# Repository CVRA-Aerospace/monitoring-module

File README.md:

Rocket monitoring module
========================
This is a compact monitoring system.
It is used for monitoring a rocket.

Main features:
-------------
 - 3-axis gyroscope
 - Two 3-axis accelerometers (one for low g and one for high g accelerations)
 - 3-axis magnetometer
 - Barometer
 - ARM controller
 - microSD card
 - 1x CAN
 - 1x UART

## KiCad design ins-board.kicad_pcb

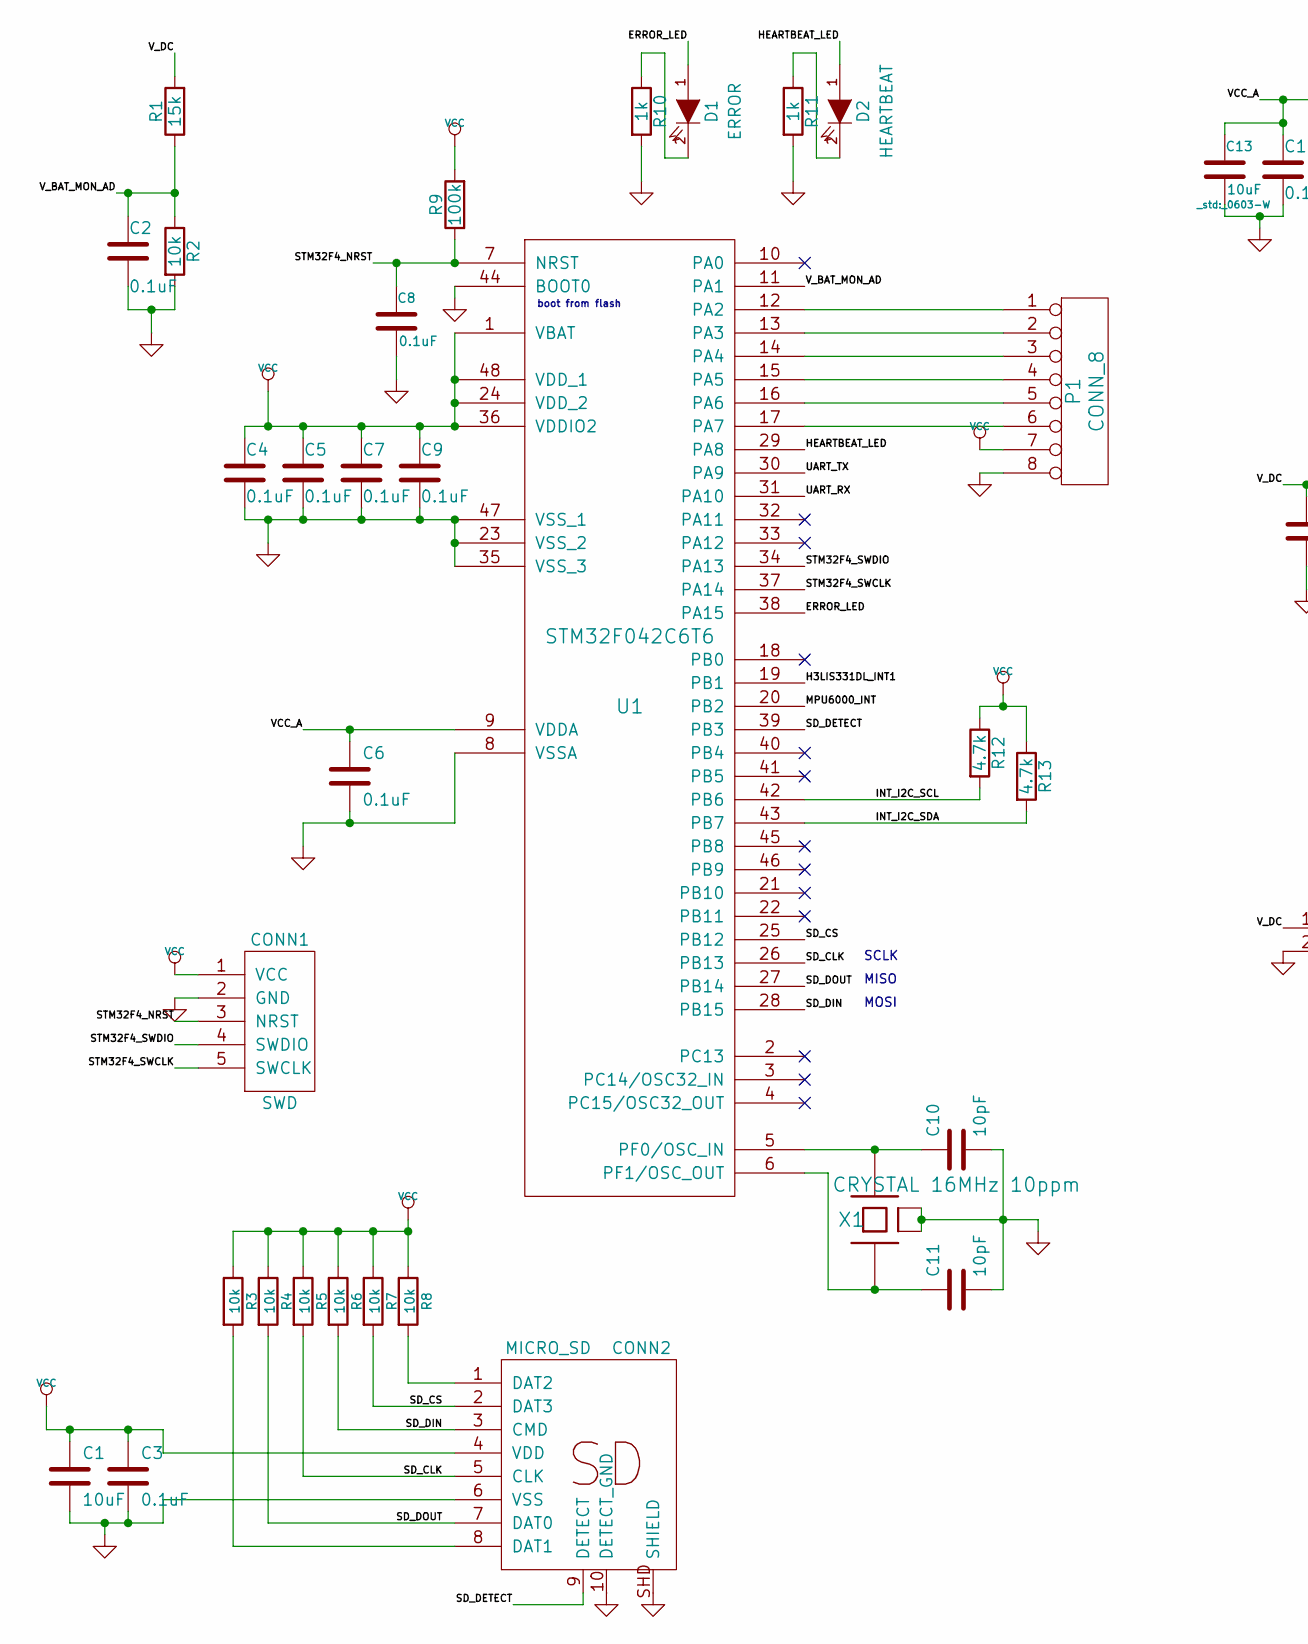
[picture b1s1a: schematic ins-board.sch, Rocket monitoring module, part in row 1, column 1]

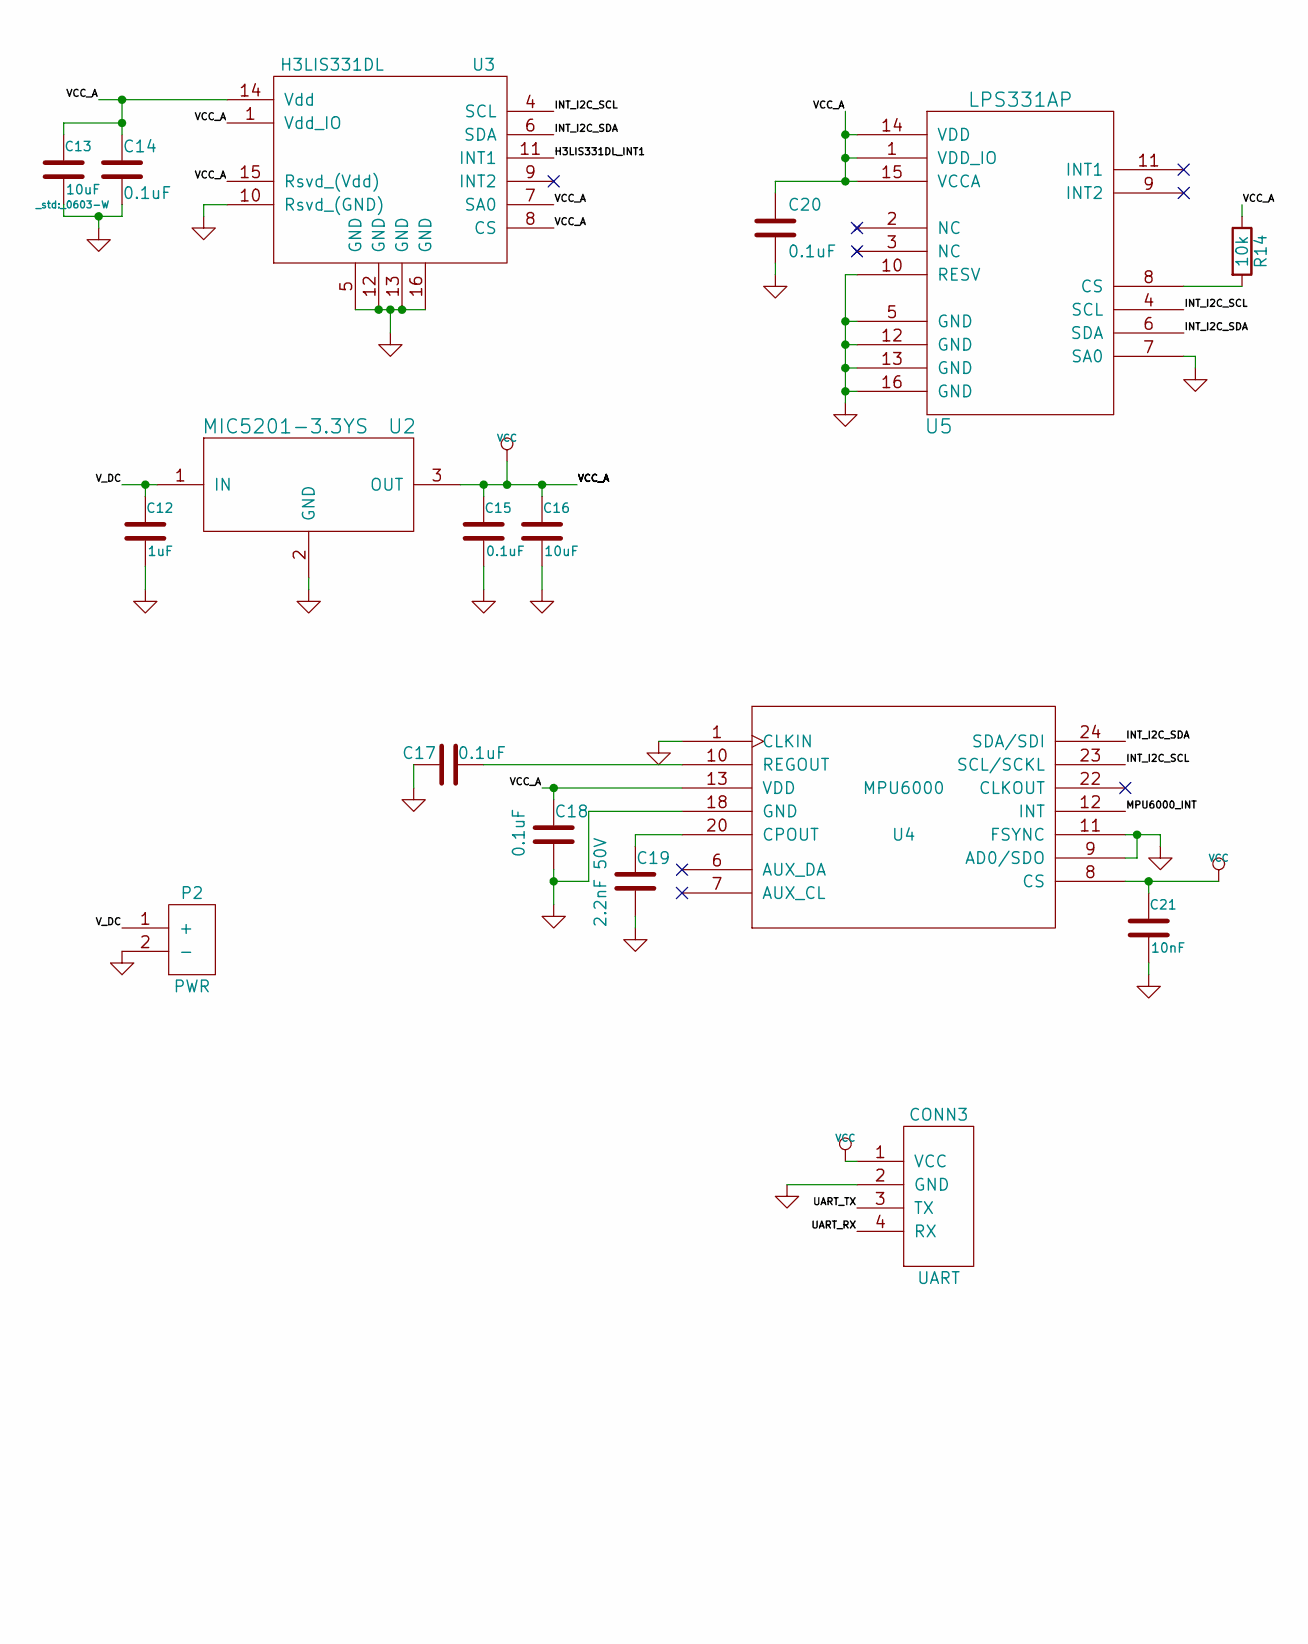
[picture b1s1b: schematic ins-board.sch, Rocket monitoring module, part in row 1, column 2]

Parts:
C1, C13, C16: 10uF; _0603-W
C2, C3, C4, C5, C6, C7, C8, C9, C14, C15, C17, C18, C20: 0.1uF; _0603-W
C10, C11: 10pF; _0603-W
C12: 1uF; _0603-W
C19: 2.2nF 50V; _0603-W
C21: 10nF; _0603-W
CONN1: SWD; _Pin2mm_5z
CONN2: MICRO_SD; _Molex-microSD-502570-0893
CONN3: UART; _Molex-PicoBlade-SMD-4
D1: ERROR; _0603-W
D2: HEARTBEAT; _0603-W
P1: CONN_8; _Solder_Pad1.27_8
P2: PWR; _Molex-PicoBlade-SMD-2
R1: 15k; _0603-W
R2, R3, R4, R5, R6, R7, R8: 10k; _0603-W
R9: 100k; _0603-W
R10, R11: 1k; _0603-W
R12, R13: 4.7k; _0603-W
R14: 10k
U1: STM32F042C6T6; _LQFP48
U2: MIC5201-3.3YS; _SOT23-3
U3: H3LIS331DL; _H3LIS331DL
U4: MPU6000; _MPU-60X0
U5: LPS331AP
X1: CRYSTAL 16MHz 10ppm; _TSX-3225-SMD-XTAL

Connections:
/ERROR_LED: D1.1 (A), U1.38 (PA15)
/H3LIS331DL_INT1: U1.19 (PB1), U3.11 (INT1)
/HEARTBEAT_LED: D2.1 (A), U1.29 (PA8)
/INT_I2C_SCL: R12.2, U1.42 (PB6), U3.4 (SCL), U4.23 (SCL/SCKL), U5.4 (SCL)
/INT_I2C_SDA: R13.2, U1.43 (PB7), U3.6 (SDA), U4.24 (SDA/SDI), U5.6 (SDA)
/MPU6000_INT: U1.20 (PB2), U4.12 (INT)
/SD_CLK: CONN2.5 (CLK), R5.2, U1.26 (PB13)
/SD_CS: CONN2.2 (DAT3), R7.2, U1.25 (PB12)
/SD_DETECT: CONN2.9 (DETECT), U1.39 (PB3)
/SD_DIN: CONN2.3 (CMD), R6.2, U1.28 (PB15)
/SD_DOUT: CONN2.7 (DAT0), R4.2, U1.27 (PB14)
/STM32F4_NRST: C8.1, CONN1.3 (NRST), R9.1, U1.7 (NRST)
/STM32F4_SWCLK: CONN1.5 (SWCLK), U1.37 (PA14)
/STM32F4_SWDIO: CONN1.4 (SWDIO), U1.34 (PA13)
/UART_RX: CONN3.4 (RX), U1.31 (PA10)
/UART_TX: CONN3.3 (TX), U1.30 (PA9)
/V_BAT_MON_AD: C2.1, R1.1, R2.1, U1.11 (PA1)
/V_DC: C12.1, P2.1 (+), R1.2, U2.1 (IN)
GND: C1.2, C2.2, C3.2, C4.2, C5.2, C6.2, C7.2, C8.2, C9.2, C10.2, C11.2, C12.2, C13.2, C14.2, C15.2, C16.2, C17.1, C18.2, C19.2, C20.2, C21.2, CONN1.2 (GND), CONN2.6 (VSS), CONN2.10 (DETECT_GND), CONN2.SHD (SHIELD), CONN3.2 (GND), CONN3.MECH (GND), P1.8, P2.2 (-), P2.MECH (GND), R2.2, R10.2, R11.2, U1.8 (VSSA), U1.23 (VSS_2), U1.35 (VSS_3), U1.44 (BOOT0), U1.47 (VSS_1), U2.2 (GND), U3.5 (GND), U3.10 (Rsvd_(GND)), U3.12 (GND), U3.13 (GND), U3.16 (GND), U4.1 (CLKIN), U4.9 (AD0/SDO), U4.11 (FSYNC), U4.18 (GND), U5.5 (GND), U5.7 (SA0), U5.10 (RESV), U5.12 (GND), U5.13 (GND), U5.16 (GND), X1.2 (case), X1.4 (case)
unnamed: C10.1, U1.5 (PF0/OSC_IN), X1.3
unnamed: C11.1, U1.6 (PF1/OSC_OUT), X1.1
unnamed: C17.2, U4.10 (REGOUT)
unnamed: C19.1, U4.20 (CPOUT)
unnamed: CONN2.1 (DAT2), R8.2
unnamed: CONN2.8 (DAT1), R3.2
unnamed: D1.2 (K), R10.1
unnamed: D2.2 (K), R11.1
unnamed: P1.1, U1.12 (PA2)
unnamed: P1.2, U1.13 (PA3)
unnamed: P1.3, U1.14 (PA4)
unnamed: P1.4, U1.15 (PA5)
unnamed: P1.5, U1.16 (PA6)
unnamed: P1.6, U1.17 (PA7)
unnamed: R14.2, U5.8 (CS)
VCC: C1.1, C3.1, C4.1, C5.1, C6.1, C7.1, C9.1, C13.1, C14.1, C15.1, C16.1, C18.1, C20.1, C21.1, CONN1.1 (VCC), CONN2.4 (VDD), CONN3.1 (VCC), P1.7, R3.1, R4.1, R5.1, R6.1, R7.1, R8.1, R9.2, R12.1, R13.1, R14.1, U1.1 (VBAT), U1.9 (VDDA), U1.24 (VDD_2), U1.36 (VDDIO2), U1.48 (VDD_1), U2.3 (OUT), U3.1 (Vdd_IO), U3.7 (SA0), U3.8 (CS), U3.14 (Vdd), U3.15 (Rsvd_(Vdd)), U4.8 (CS), U4.13 (VDD), U5.1 (VDD_IO), U5.14 (VDD), U5.15 (VCCA)

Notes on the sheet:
boot from flash
SCLK
MOSI
MISO

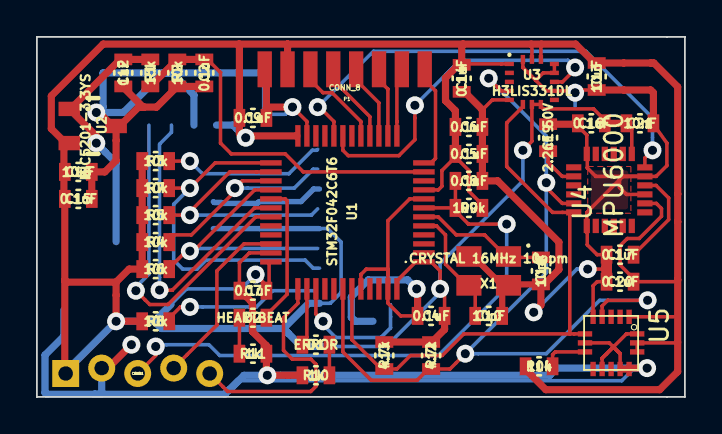
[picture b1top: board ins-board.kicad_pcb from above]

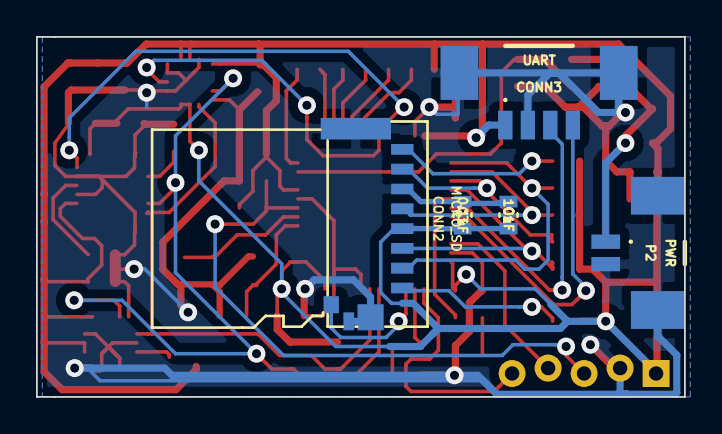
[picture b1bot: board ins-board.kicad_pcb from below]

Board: 2 copper layers, 36.0 x 20.0 mm, 48 parts (5 on the bottom side), 35 nets.

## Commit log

2015-03-25 rocket board
2015-03-25 schematics
2015-03-25 Use kicad library fork of CVRA Aerospace
2015-03-25 stm32f042
2015-03-25 Done
2015-03-25 component values
2015-03-26 sd-card fix
2015-03-26 remove optional components
2015-03-26 references
2015-03-26 pcb + footprints
2015-03-26 new libs
2015-03-28 Add pressure sensor (sch) & fix drc violations
2015-03-28 Generate netlist
2015-03-28 Component placement on PCB
2015-03-28 Correct microSD connector footprint & update component placement
2015-03-28 update sd-card footprint
2015-03-29 Replace components to ease routing
2015-03-29 Replace components to ease routing (2)
2015-03-29 Routing
2015-03-29 PCB review + corrections
2015-03-30 Update pdf
2015-03-31 mask for PCB manufacturing
2015-04-08 missing Vcc connection
